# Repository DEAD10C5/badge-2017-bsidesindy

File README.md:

## BSidesIndy 2017 Badge

We did this as a workshop during @indybsides in March 2017.

See the wiki for more information.

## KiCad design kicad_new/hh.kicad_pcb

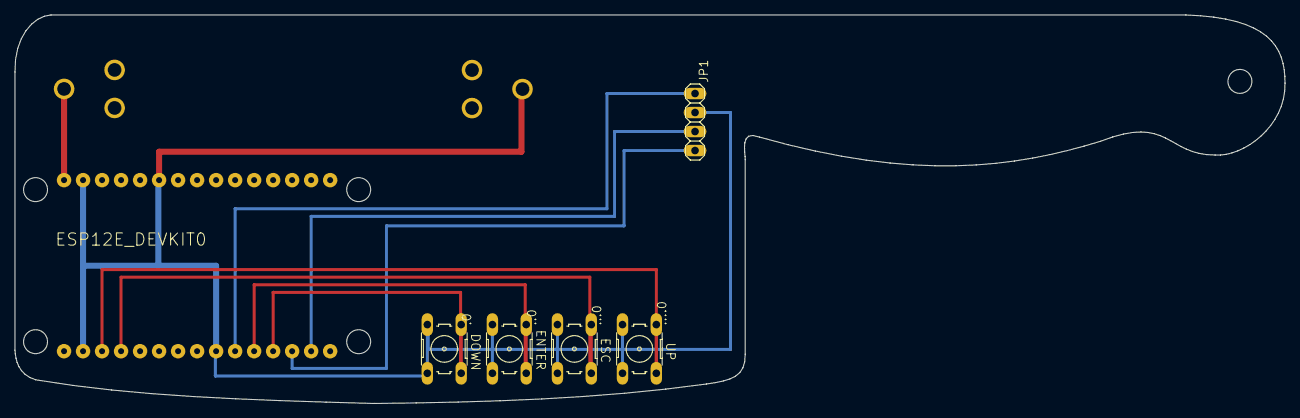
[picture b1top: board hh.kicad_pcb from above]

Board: 6 copper layers, 169.7 x 51.9 mm, 8 parts (1 on the bottom side), 9 nets.

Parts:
.0, ..0, ...0, ....0: B3F-10XX
@HOLE0: (no value)
BT1: BATTERY_18650-HOLDER
ESP12E_DEVKIT0: ESP12E_DEVKIT
JP1: OLED; 1X04

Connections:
unnamed: .0.3, .0.4, ..0.3, ..0.4, ...0.3, ...0.4, ....0.3, ....0.4, BT1.GND@1, ESP12E_DEVKIT0.GND@0, ESP12E_DEVKIT0.GND@1, ESP12E_DEVKIT0.GND@2, ESP12E_DEVKIT0.GND@3, JP1.2
unnamed: .0.1, .0.2, ESP12E_DEVKIT0.D3
unnamed: ESP12E_DEVKIT0.3V3@1, JP1.1
unnamed: BT1.PWR@1, ESP12E_DEVKIT0.VIN
unnamed: ESP12E_DEVKIT0.D1, JP1.3
unnamed: ESP12E_DEVKIT0.D2, JP1.4
unnamed: ..0.1, ..0.2, ESP12E_DEVKIT0.D4
unnamed: ...0.1, ...0.2, ESP12E_DEVKIT0.RX
unnamed: ....0.1, ....0.2, ESP12E_DEVKIT0.TX

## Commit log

2016-08-17 Badge Files
    Initial Eagle Badge Files
2016-08-30 Add files via upload
    Updated board with smaller footprint
2016-08-31 Add files via upload
    Latest version
2016-08-31 Add files via upload
    Now with serial breakout! I'm not sure that the footprint for the radio is correct - need to double-check the pintout on the module spec sheet...
2016-12-10 badge pcb art
2016-12-10 minor updates
2016-12-17 pcb updates
2016-12-28 graphics updates
2017-01-05 Created new SVG with simplified vectors and outline
2017-01-05 Created outline and silkscreen artwork, imported both to kicad and created board
2017-01-08 cleanup
2017-01-08 eagle schematic
2017-01-23 adding lua stuff
2017-01-25 Update PartsList.md
    added batteries, make a table
2017-01-25 Update PartsList.md
    fix table
2017-01-25 add optional parts
2017-02-09 change source of ESP8266 for shorter ordering time
2017-02-27 Update PartsList.md
    added micro USB cable
2017-03-01 add sample arduino code
2017-03-02 prototyping updates
2017-03-03 refactoring, added first button
2017-03-03 tweak
2017-03-05 button test sketch
2017-03-10 Updated instructions for OS X
2017-03-10 Fixed typos in readme
2017-03-13 updates to eagle files
2017-03-16 design updates
2017-03-17 Update README.md
    added battery holder info
2017-03-17 images and brd update
2017-03-17 revise component placement in eagle
2017-03-17 add silkscreen text in eagle
2017-03-17 wiring 1
2017-03-17 wiring 2
2017-03-17 adding OSH park drc for reference
2017-03-17 fix eagle drc error
2017-03-18 testing final design
2017-03-18 tweaks
2017-03-18 arduino sketch cleanup
2017-03-18 Added battery clips, fixed VIN, moved switches closer together to accommodate the battery clips, added a ground plane under the radio.
2017-03-18 Update PartsList.md
    changed battery holder
2017-03-18 Update README.md
    change battery holder
2017-03-19 Add files via upload
    Latest Update
2017-03-19 gerber files
2017-03-19 Update PartsList.md
    change OLED source, must have Vcc pin on far left
2017-03-19 Create LICENSE
2017-03-19 silkscreen updates
2017-03-19 silkscreen placement
2017-03-19 Major changes to placement of components
2017-03-19 Trace Revisions
2017-03-19 silkscreen edits
2017-03-19 Artwork
    Added BSides Indy artwork
2017-03-19 Modified switch labels
2017-04-03 Added WiFi Scanning code
2017-04-03 Code Update
    Allows you to scan for WiFi networks, scroll through the networks
    (UP/DOWN buttons), re-scan networks (ESC button), and connect to a
    network with open authentication (ENTER button)
2017-04-03 Better WiFi error handling
    Better WiFi error handling
2017-04-04 Allow to disconnect after WiFi is connected
    Pressing ESC during or after WiFi connection will re-scan and allow you
    to connect to another network.
2017-06-09 Latest Updates
2018-04-04 cleanup first release
2022-08-24 Add .whitesource configuration file
2022-10-08 Add .whitesource configuration file (#4)
2022-10-08 convert eagle to KiCAD
2022-10-08 convert eagle to KiCAD (#5)
2022-10-08 add kibot action
2022-10-08 add kibot action (#6)
    * add kibot action
    * add kibot action
    * add kibot action
2022-10-08 add kibot action (#7)
2023-12-15 Add renovate.json
